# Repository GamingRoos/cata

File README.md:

# Cata Keyboard

Cata is a 34 key ortholinear keyboard, powered by a [Waveshare RP2040-Zero](https://www.waveshare.com/rp2040-zero.htm).

It uses [Gateron KS-33 Low Profile 3.0 keyswitches](https://nuphy.com/products/gateron-low-profile-3-0-switches) with 19mm x 19mm spacing.

The PCB design is akin to the [Sha Keyboard](https://github.com/skarrmann/sha), but with fewer keys and different keyswitches.

## Project structure

* [`gerbers`](gerbers): Gerber files for PCB manufacturing
* [`graphics`](graphics): Source assets for PCB silkscreen
* [`kicad`](kicad): KiCad project files (schematics and PCB designs)
* [`kicad-libraries`](kicad-libraries): KiCad components and footprints
* [`images`](images): Images for project documentation

## PCBs

**Each build uses two copies of the main PCB and one copy of the top plate PCB.**

The main PCB is used as the logical PCB. A second copy of the main PCB is used a bottom plate, by flipping it the long way and screwing it directly to the logical PCB.

The plate PCB cover the dev board and diodes. It has cutouts which fit the boot and reset buttons on the dev board.

## Keyboard firmware

* KMK
    * Setup instructions and basic configuration is in this repo: [`firmware/kmk`](firmware/kmk)
* [QMK](https://github.com/qmk/qmk_firmware/tree/master/keyboards/cata)
* QMK/VIAL VIAL configs here: [`firmware/vial`](firmware/vial)
## Bill of materials

Part | Purpose | Quantity | Notes
---- | ------- | -------- | ---------
Main PCB  | logical PCB, bottom plate | 2 | Send Gerber zip files to [JLCPCB](https://jlcpcb.com/)
Top plate PCB  | cover dev board and diodes  | 1 | 
Waveshare RP2040-Zero | Microcontroller board | 1 |
1N4148 SOD-123 | Diodes for keyboard row-column matrix | 34 |
Gateron KS-33 Low Profile 3.0 Keyswitches |  | 34 | [Several options available from Nuphy](https://nuphy.com/products/gateron-low-profile-3-0-switches)
MX Low Profile Keycaps | | 34 | Use low profile keycaps which fit 19mm x 19mm spacing
M2 5mm screws | Screws PCBs together | 12 |
M2 6mm spacers | Spacers between logical PCB and top plates | 2 |
M2 nuts | Holds the top screws between the bottom plate and logical PCB | 8 |

## PCB manufacturing settings

These are the manufacturing settings I used when ordering from JLCPCB:

* **Base Material**: FR4
* **Layers**: 2
* **Dimensions**: (whatever the gerber file specifies)
* **PCB Qty**: 5
* **Different Design**: 1
* **Delivery Format**: Single PCB
* **PCB Thickness**: 1.6
* **PCB Color**: Black
* **Silkscreen**: White
* **Surface Finish**: LeadFree HASL-RoHS
* **Outer Copper Weight**: 1 oz
* **Gold Fingers**: No
* **Confirm Production File**: No
* **Flying Probe Test**: Fully Test
* **Castellated Holes**: No
* **Mark on PCB**: Remove Mark

## Build tips

* Before starting, check if the PCBs are warped, and bend them to be perfectly flat before soldering.
* Make sure the diodes are oriented correctly, cathode on the side with the line! The diodes are very close together, so narrow tweasers can help position them.
    * 
* Make sure the RP2040-Zero is soldered **buttons on top**. The pinout labels printed on the PCB should align with those printed on the dev board.
    * 
    * 

## KiCad project notes

The top plate was generated with the [Horizon Board Producer KiCad plugin](https://github.com/skarrmann/horizon#kicad-project-notes).

## Revision history

* Cata 1.0 (2025-07-27)
    * Initial Gateron KS-33 Low Profile 3.0 switch PCB design

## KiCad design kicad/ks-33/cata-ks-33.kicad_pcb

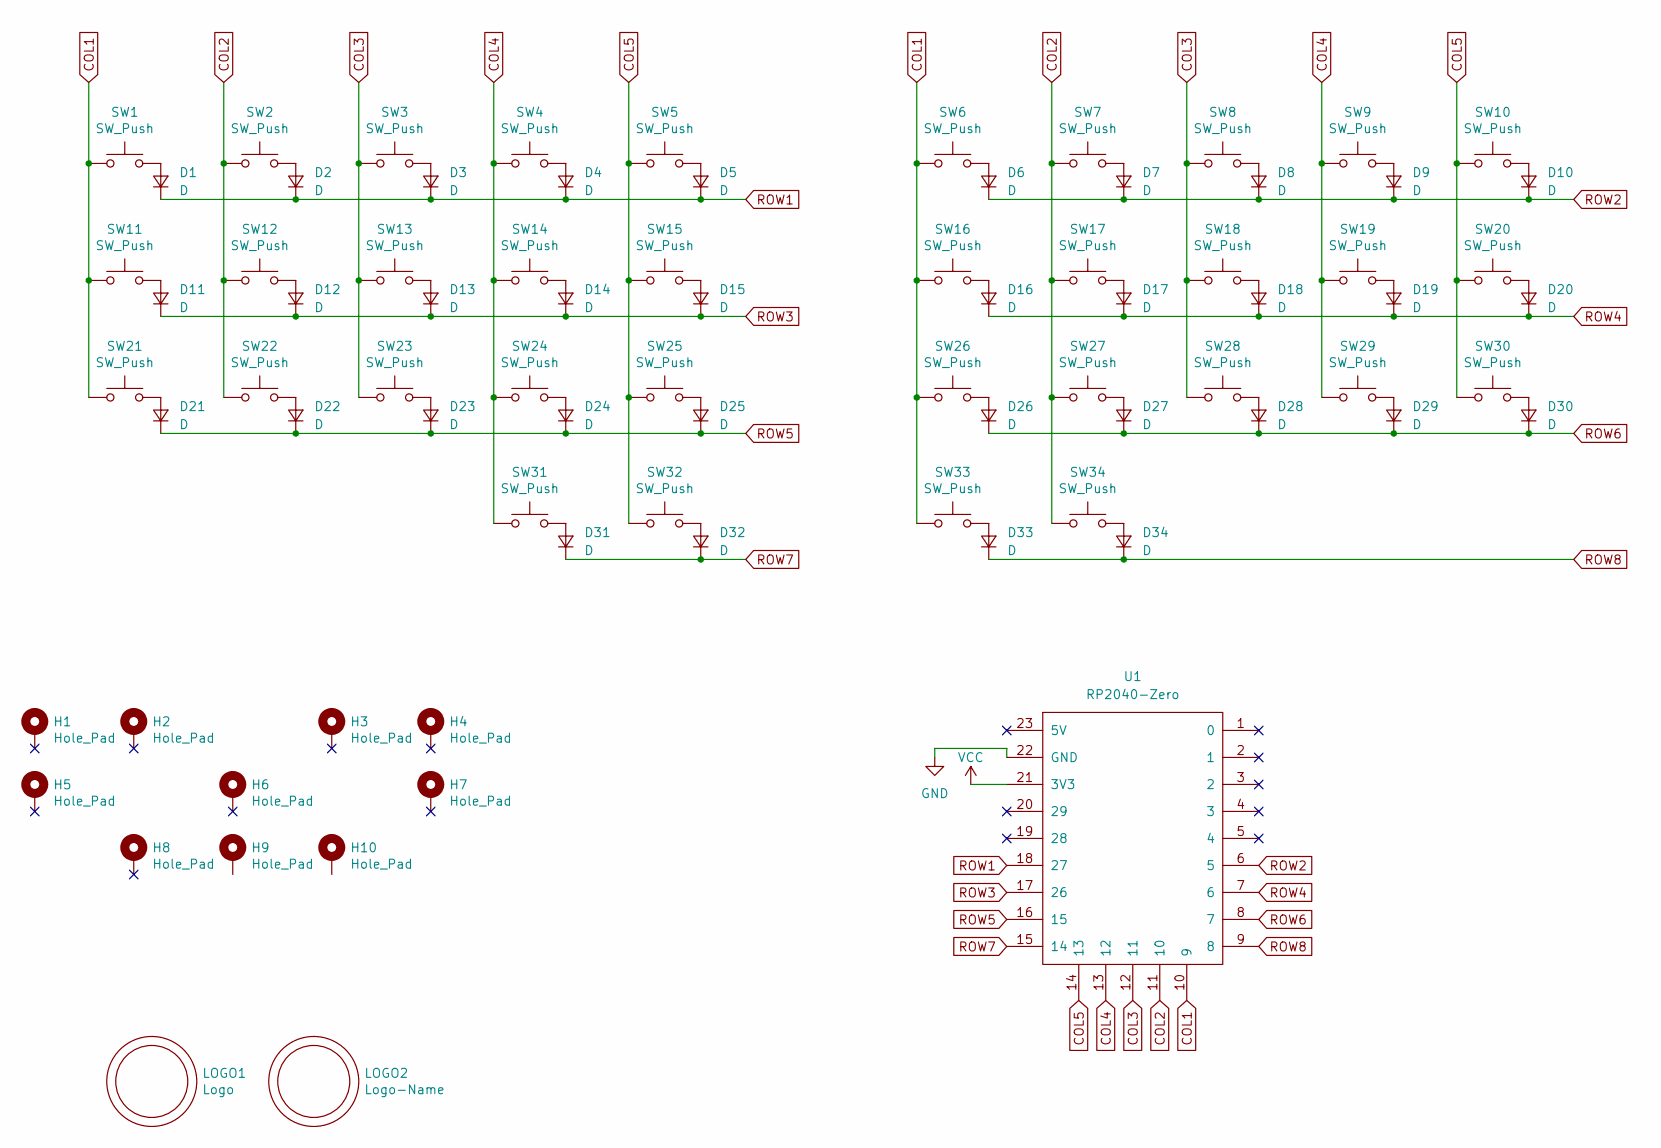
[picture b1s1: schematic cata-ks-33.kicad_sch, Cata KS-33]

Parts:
D1, D2, D3, D4, D5, D6, D7, D8, D9, D10, D11, D12, D13, D14, D15, D16, D17, D18, D19, D20, D21, D22, D23, D24, D25, D26, D27, D28, D29, D30, D31, D32, D33, D34: D; D_SOD-123
H1, H2, H3, H4, H5, H6, H7, H8, H9, H10: Hole_Pad; Mount_M2
LOGO1: Logo; Logo_Cata
LOGO2: Logo-Name; Logo_Cata_Name
SW1, SW2, SW3, SW4, SW5, SW6, SW7, SW8, SW9, SW10, SW11, SW12, SW13, SW14, SW15, SW16, SW17, SW18, SW19, SW20, SW21, SW22, SW23, SW24, SW25, SW26, SW27, SW28, SW29, SW30, SW31, SW32, SW33, SW34: SW_Push; SW_KS33_Reverse_Cutout
U1: RP2040-Zero; RP2040-Zero_SMD

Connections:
COL1: SW1.1, SW6.1, SW11.1, SW16.1, SW21.1, SW26.1, SW33.1, U1.10 (9)
COL2: SW2.1, SW7.1, SW12.1, SW17.1, SW22.1, SW27.1, SW34.1, U1.11 (10)
COL3: SW3.1, SW8.1, SW13.1, SW18.1, SW23.1, SW28.1, U1.12 (11)
COL4: SW4.1, SW9.1, SW14.1, SW19.1, SW24.1, SW29.1, SW31.1, U1.13 (12)
COL5: SW5.1, SW10.1, SW15.1, SW20.1, SW25.1, SW30.1, SW32.1, U1.14 (13)
GND: U1.22 (GND)
unnamed: D1.2 (A), SW1.2
unnamed: D2.2 (A), SW2.2
unnamed: D3.2 (A), SW3.2
unnamed: D4.2 (A), SW4.2
unnamed: D5.2 (A), SW5.2
unnamed: D6.2 (A), SW6.2
unnamed: D7.2 (A), SW7.2
unnamed: D8.2 (A), SW8.2
unnamed: D9.2 (A), SW9.2
unnamed: D10.2 (A), SW10.2
unnamed: D11.2 (A), SW11.2
unnamed: D12.2 (A), SW12.2
unnamed: D13.2 (A), SW13.2
unnamed: D14.2 (A), SW14.2
unnamed: D15.2 (A), SW15.2
unnamed: D16.2 (A), SW16.2
unnamed: D17.2 (A), SW17.2
unnamed: D18.2 (A), SW18.2
unnamed: D19.2 (A), SW19.2
unnamed: D20.2 (A), SW20.2
unnamed: D21.2 (A), SW21.2
unnamed: D22.2 (A), SW22.2
unnamed: D23.2 (A), SW23.2
unnamed: D24.2 (A), SW24.2
unnamed: D25.2 (A), SW25.2
unnamed: D26.2 (A), SW26.2
unnamed: D27.2 (A), SW27.2
unnamed: D28.2 (A), SW28.2
unnamed: D29.2 (A), SW29.2
unnamed: D30.2 (A), SW30.2
unnamed: D31.2 (A), SW31.2
unnamed: D32.2 (A), SW32.2
unnamed: D33.2 (A), SW33.2
unnamed: D34.2 (A), SW34.2
ROW1: D1.1 (K), D2.1 (K), D3.1 (K), D4.1 (K), D5.1 (K), U1.18 (27)
ROW2: D6.1 (K), D7.1 (K), D8.1 (K), D9.1 (K), D10.1 (K), U1.6 (5)
ROW3: D11.1 (K), D12.1 (K), D13.1 (K), D14.1 (K), D15.1 (K), U1.17 (26)
ROW4: D16.1 (K), D17.1 (K), D18.1 (K), D19.1 (K), D20.1 (K), U1.7 (6)
ROW5: D21.1 (K), D22.1 (K), D23.1 (K), D24.1 (K), D25.1 (K), U1.16 (15)
ROW6: D26.1 (K), D27.1 (K), D28.1 (K), D29.1 (K), D30.1 (K), U1.8 (7)
ROW7: D31.1 (K), D32.1 (K), U1.15 (14)
ROW8: D33.1 (K), D34.1 (K), U1.9 (8)
VCC: U1.21 (3V3)

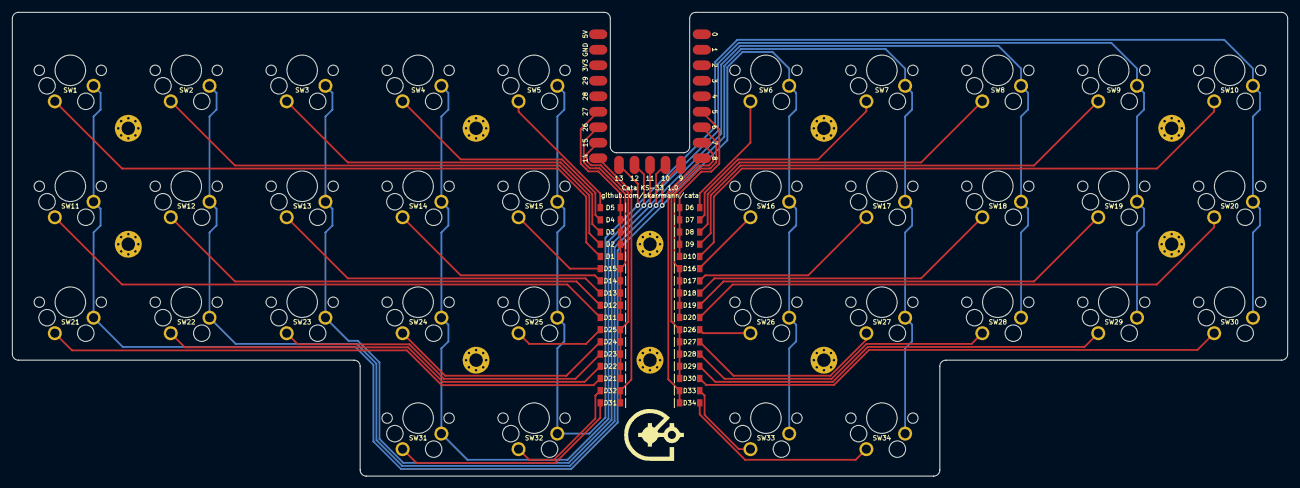
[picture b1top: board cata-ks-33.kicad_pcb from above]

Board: 2 copper layers, 209.0 x 76.0 mm, 81 parts (1 on the bottom side), 47 nets.

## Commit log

2025-07-28 Fix diode alignment, generate gerbers
2025-07-28 Move logo and name silkscreen on PCB
2025-08-04 Clean up readme.
2025-08-09 Implement KMK firmware
2025-08-09 Add build images and add to readme
2025-08-09 Remove left shift as oneshot ignore key
2025-08-16 Note QMK firmware is coming soon
2025-09-11 Add link to QMK firmware.
2025-09-24 Added Vial support for QMK firmware
2025-09-24 Vial Build files
